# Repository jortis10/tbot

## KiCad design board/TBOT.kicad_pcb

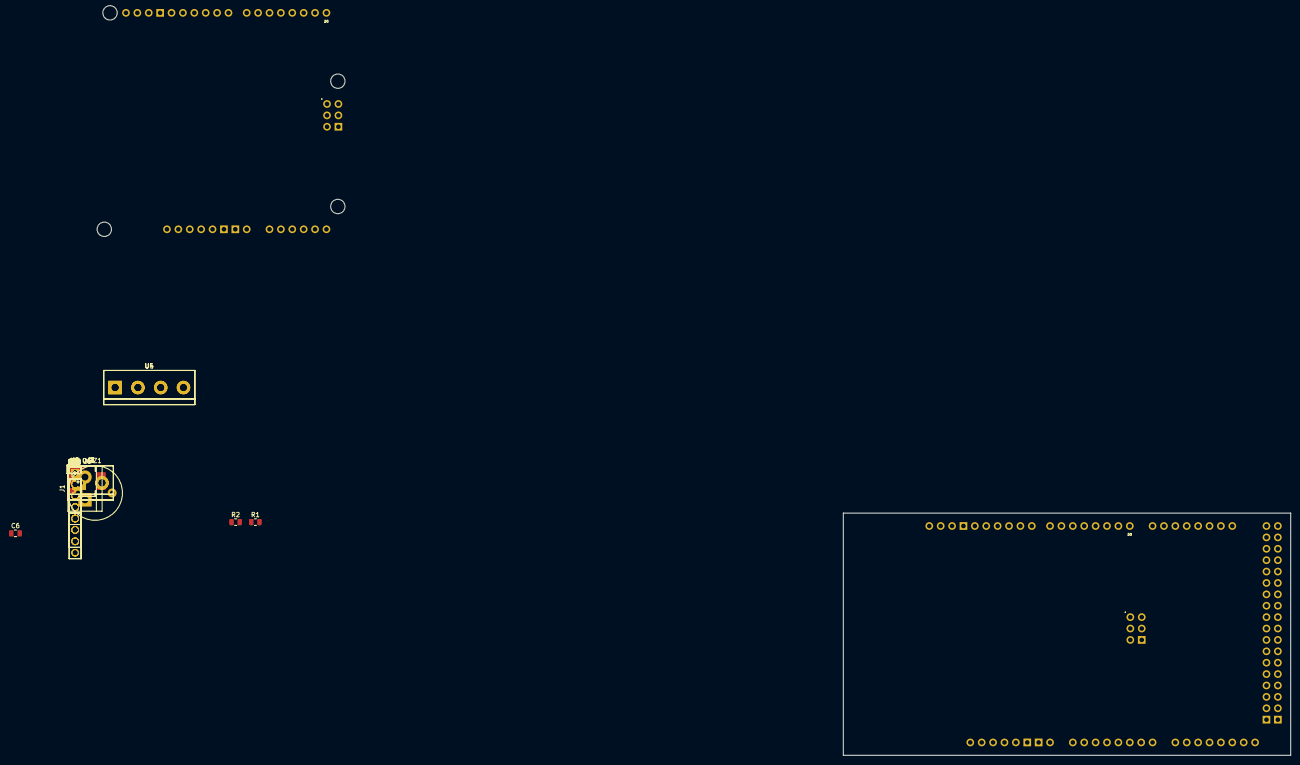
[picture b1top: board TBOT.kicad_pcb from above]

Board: 2 copper layers, 99.8 x 54.0 mm, 49 parts (0 on the bottom side), 15 nets, no tracks yet.

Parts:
BZ1: Buzzer; Buzzer_12x9.5RM7.6
C1, C2, C7#2, C11: 100nF/10V; C_0805_2012Metric
C3: 10uF/20V; C_0805_2012Metric
C4: 0.33uF/20V; C_0805_2012Metric
C5: 0.1uF/10V; C_0805_2012Metric
C6, C7, C8, C9: 1uF; C_0805_2012Metric
C6#2: 100nF/20V; C_0805_2012Metric
D1: BZX384A10Q; D_SOD-323
D2: 4.7V; D_0805_2012Metric
D3: LED; LED_0805_2012Metric
J1: BATTERY; TerminalBlock_bornier-2_P5.08mm
J2: Conn_01x04; PinSocket_1x04_P2.54mm_Vertical
J2#2: R_POWER; TerminalBlock_bornier-2_P5.08mm
J3: L_POWER; TerminalBlock_bornier-2_P5.08mm
J4: OLED_I2C; PinSocket_1x05_P2.54mm_Vertical
J5: RTC_I2C; PinSocket_1x04_P2.54mm_Vertical
J6: GP_I2C; PinSocket_1x04_P2.54mm_Vertical
Q1: ZXMP3A16G; SOT-223-3_TabPin2
R1, R2, R9: R; R_0805_2012Metric
R3, R12: 0R NI; R_0805_2012Metric
R4: 100K; R_0805_2012Metric
R5: 9.1K; R_0805_2012Metric
R5#2, R6#2, R10, R11: 10k; R_0805_2012Metric
R6: 3.6K; R_0805_2012Metric
R7: 0.01R; R_0805_2012Metric
R8: 33k; R_0805_2012Metric
U1, U7: MPU-6050_Module; PinSocket_1x08_P2.54mm_Vertical
U1#2: TBOT_Motor_Driver_R; PinHeader_1x07_P2.54mm_Vertical
U2: TBOT_Motor_Driver_L; PinHeader_1x07_P2.54mm_Vertical
U3: INA169; SOT-23-5
U4: CPR_Encoder_R; TerminalBlock_bornier-4_P5.08mm
U5: CPR_Encoder_L; TerminalBlock_bornier-4_P5.08mm
U6: uA7805; SOT-223
U7#2: MCP1703A-5002_SOT23; SOT-23
XA1: Arduino_Mega2560_Shield
XA2: Arduino_Uno_Shield

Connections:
+3V3: C11.1, J4.1, J6.1, R10.1, R11.1, U7.1 (VCC), XA1.3V3 (3.3V)
+5V: C1.1, C5.1, C7#2.1, U3.5 (V+), U4.1 (V_SENSOR), U5.1 (V_SENSOR), U6.3 (OUT), U7#2.2 (VO), XA1.5V1 (5V)
+12V: C3.1, C4.1, C6#2.1, J2#2.1, J3.1, R7.2, R9.1, R12.1, U3.3 (+), U6.1 (IN), U7#2.3 (VI)
GND: C11.2, U7#2.1 (GND)
I2C_SCL: J4.3, J5.1, J6.3, R11.2, U7.3 (SCL), XA1.SCL
I2C_SDA: J4.4, J5.2, J6.4, R10.2, U7.4 (SDA), XA1.SDA
I_MEAS: R8.1, U3.1, XA1.A2
unnamed: D1.1 (K), Q1.3 (S), R3.2, R7.1, U3.4 (-)
unnamed: D1.2 (A), Q1.1 (G), R4.1
unnamed: D3.2 (A), R9.2
unnamed: Q1.2 (D), R3.1
unnamed: R12.2, XA1.VIN
OLED_RST: C1.2, C2.2, C3.2, C4.2, C5.2, C6#2.2, C7#2.2, D2.2 (A), D3.1 (K), J1.2, J2#2.2, J3.2, J4.2, J4.5, J5.4, J6.2, R4.2, R6.2, R8.2, U1#2.2 (GND), U2.2 (GND), U3.2 (GND), U4.2 (GND), U5.2 (GND), U6.2 (GND), U6.4 (GND), U7.2 (GND), XA1.GND1 (GND), XA1.GND2 (GND), XA1.GND3 (GND), XA1.GND5 (GND), XA1.GND6 (GND)
V_BAT: J1.1, R5.1
V_BAT_MEAS: C2.1, D2.1 (K), R5.2, R6.1, XA1.A1

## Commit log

2023-01-29 Initial commit for electronic board
